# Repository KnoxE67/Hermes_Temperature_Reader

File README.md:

# Hermes_Temperature_Reader
Building a Custom Hermes project with a LM75AD_118, XIAO RP2040, and a 0.96” 128 X 64 OLED DISPLAY

# What?

So this project is about making something clean, cool, and something Im going to use for a long time.
It uses a PCB, a XIAO RP2040, a SSD1306 OLED Display, a LM75AD,118 Temperature sensor, 
One 0.1 µF Ceramic Capacitor, Two 4.7k ohm Resistors, and One 10k ohm Resistor.

# Why?

So I did the project so that I could learn how to build something using a Datasheet which I havn't done without help before,
cool, nice, and something I would actual use unlike the Blueprint Projects: Custom Hackpad and RP2040 DevBoard.
I also did this project because I was bored and waiting for my other project Pathfinder to get reviewed and approved.

# Pictures

3D Model:

PCB:

Schematic: 

# BOM

| Name                                                                       | Purpose                                                                                                                                   | Quantity | Total Cost (USD) | Link                                                                                    | Distributor |
|----------------------------------------------------------------------------|-------------------------------------------------------------------------------------------------------------------------------------------|----------|------------------|-----------------------------------------------------------------------------------------|-------------|
| PCB                                                                        | To connect everything together                                                                                                            | 5        | 5.31             |                                                                                         | JLCPCB      |
| 10 kOhms ±5% 0.25W, 1/4W Through Hole Resistor Axial Carbon Film           | Used to dampen the Temperature Sensors data, again got 9 extra because it was cheaper                                                     | 10       | 0.31             | https://www.digikey.com/en/products/detail/stackpole-electronics-inc/CF14JT10K0/1741265 | Digikey     |
| 4.7 kOhms ±5% 0.5W, 1/2W Through Hole Resistor Axial Carbon Film           | To pull up the SDA and SCL, got 8 extra becausae it was cheaper                                                                           | 10       | 0.43             | https://www.digikey.com/en/products/detail/stackpole-electronics-inc/CF12JT4K70/1741152 | Digikey     |
| 0.1 µF ±10% 25V Ceramic Capacitor X7R 0603 (1608 Metric)                   | It's a Cermanic Capacitor for the Temperature Sensor. Got some extra because again I'm going to manually solder these by hand.            | 10       | 0.52             | https://www.digikey.com/en/products/detail/kemet/C0603C104K3RACTU/416044                | Digikey     |
| LM75AD,118 Temperature Sensor Digital, Local -55°C ~ 125°C 11 b 8-SO       | To get the temperature where ever it is powered, also got 1 extra because I'm going to be soldering this manually and not through JLCPCB. | 2        | 1.42             | https://www.digikey.com/en/products/detail/nxp-usa-inc/LM75AD-118/1692795               | Digikey     |
| RP2040 XIAO RP2040 - ARM® Cortex®-M0+ MCU 32-Bit Embedded Evaluation Board | This is used to power the board                                                                                                           | 1        | 5.15             | https://www.digikey.com/en/products/detail/seeed-technology-co-ltd/102010428/14672129   | Digikey     |

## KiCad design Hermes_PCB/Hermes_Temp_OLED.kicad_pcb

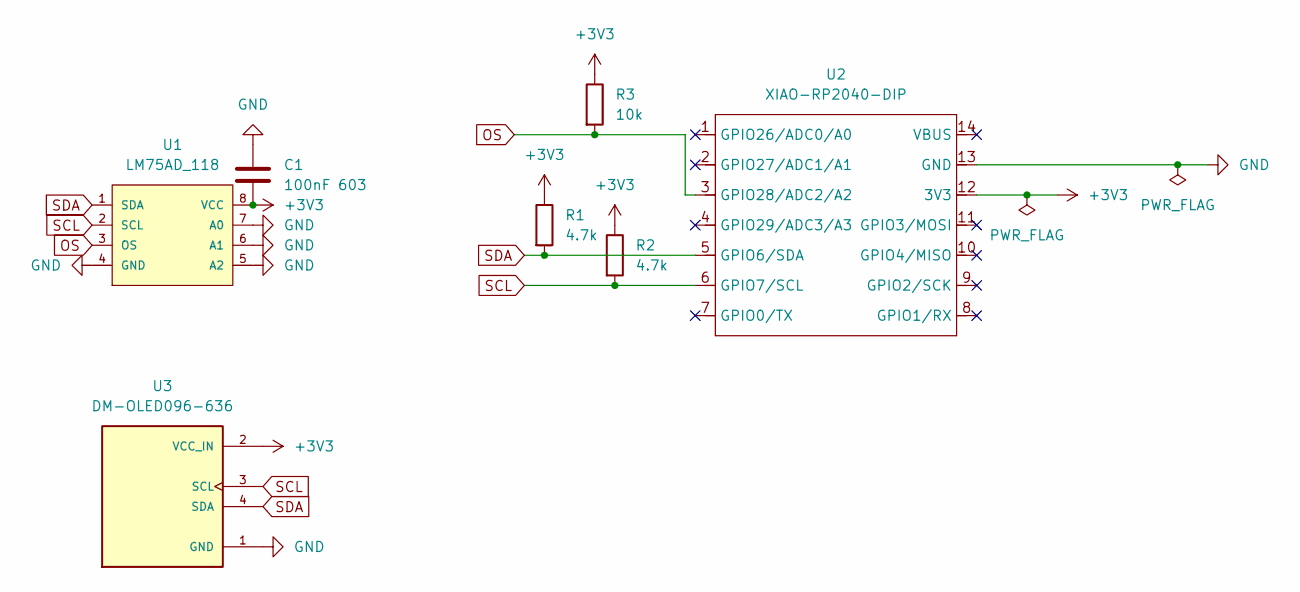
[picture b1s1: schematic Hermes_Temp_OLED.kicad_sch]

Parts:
C1: 100nF 603; C_0603_1608Metric
R1, R2: 4.7k; R_Axial_DIN0204_L3.6mm_D1.6mm_P5.08mm_Vertical
R3: 10k; R_Axial_DIN0204_L3.6mm_D1.6mm_P5.08mm_Vertical
U1: LM75AD_118; MPN LM75AD,118
U2: XIAO-RP2040-DIP
U3: DM-OLED096-636; MODULE_DM-OLED096-636; PARTREV 2018-09-10

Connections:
+3V3: C1.2, R1.1, R2.1, R3.1, U1.8 (VCC), U2.12 (3V3), U3.2 (VCC_IN)
GND: C1.1, U1.4 (GND), U1.5 (A2), U1.6 (A1), U1.7 (A0), U2.13 (GND), U3.1 (GND)
OS: R3.2, U1.3 (OS), U2.3 (GPIO28/ADC2/A2)
SCL: R2.2, U1.2 (SCL), U2.6 (GPIO7/SCL), U3.3 (SCL)
SDA: R1.2, U1.1 (SDA), U2.5 (GPIO6/SDA), U3.4 (SDA)

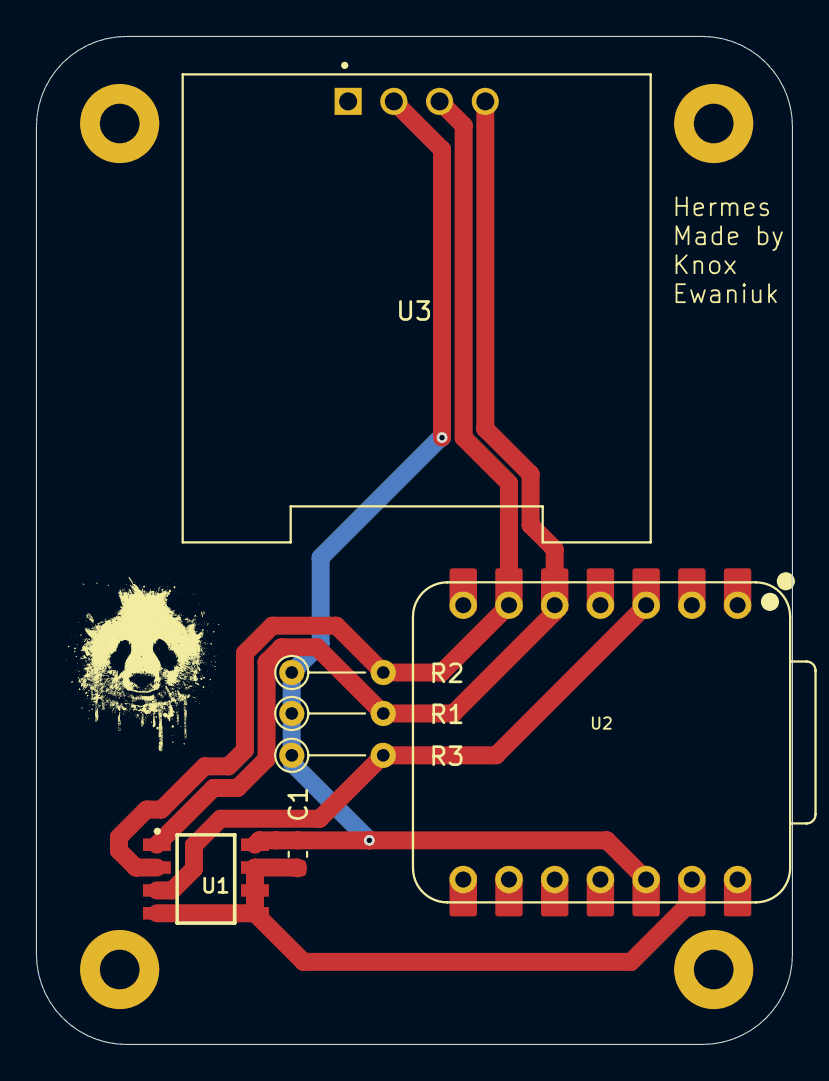
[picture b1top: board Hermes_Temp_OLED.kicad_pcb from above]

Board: 2 copper layers, 42.0 x 56.0 mm, 7 parts (0 on the bottom side), 5 nets.
